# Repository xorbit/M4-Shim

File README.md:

# M4-Shim
ARM Cortex M4 shim for PoE-FeatherWing, functionally equivalent to Feather M4 Express

You can buy it now on [Tindie](https://www.tindie.com/products/silicognition/m4-shim/)
or on [Amazon](https://www.amazon.com/M4-Shim-Feather-PoE-FeatherWing-Ultra-Compact-Vertical/dp/B0971PKDV7/)!

### Description

This is an adaptation of the excellent
[Adafruit Feather M4 Express](https://github.com/adafruit/Adafruit-Feather-M4-Express-PCB),
redesigned specifically for use with the equally excellent
[PoE-FeatherWing](https://hackaday.io/project/168356-poe-featherwing).

The goal was to create a compact system with Power over Ethernet, Ethernet connectivity and
a powerful processor capable of supporting [CircuitPython](https://circuitpython.org/).
Because of the bulky RJ45 jack and flyback transformer on the PoE-FeatherWing, it was not
possible to mount a traditional Feather on top.  This redesign takes the relevant circuitry
of the Adafruit Feather M4 Express and shapes it so it fits in the gaps between the
tall components of the PoE-FeatherWing.  This way it can be mounted on top for an extremely
compact solution.

The only thing missing versus the Feather M4 Express is the battery support circuitry,
which did not seem necessary in a PoE design.

The hardware is sold with the [UF2 bootloader](https://github.com/adafruit/uf2-samdx1)
and [CircuitPython](https://github.com/adafruit/circuitpython) pre-installed.

### License

This redesign by Silicognition LLC is licensed as Creative Commons Attribution/Share-Alike,
just like the Adafruit Feather M4 Express it is based on.

Original Adafruit license statement:

Adafruit invests time and resources providing this open source design, please support Adafruit and open-source hardware by purchasing products from [Adafruit](https://www.adafruit.com)!

Designed by Limor Fried/Ladyada for Adafruit Industries.

Creative Commons Attribution/Share-Alike, all text above must be included in any redistribution. See LICENSE for additional details.

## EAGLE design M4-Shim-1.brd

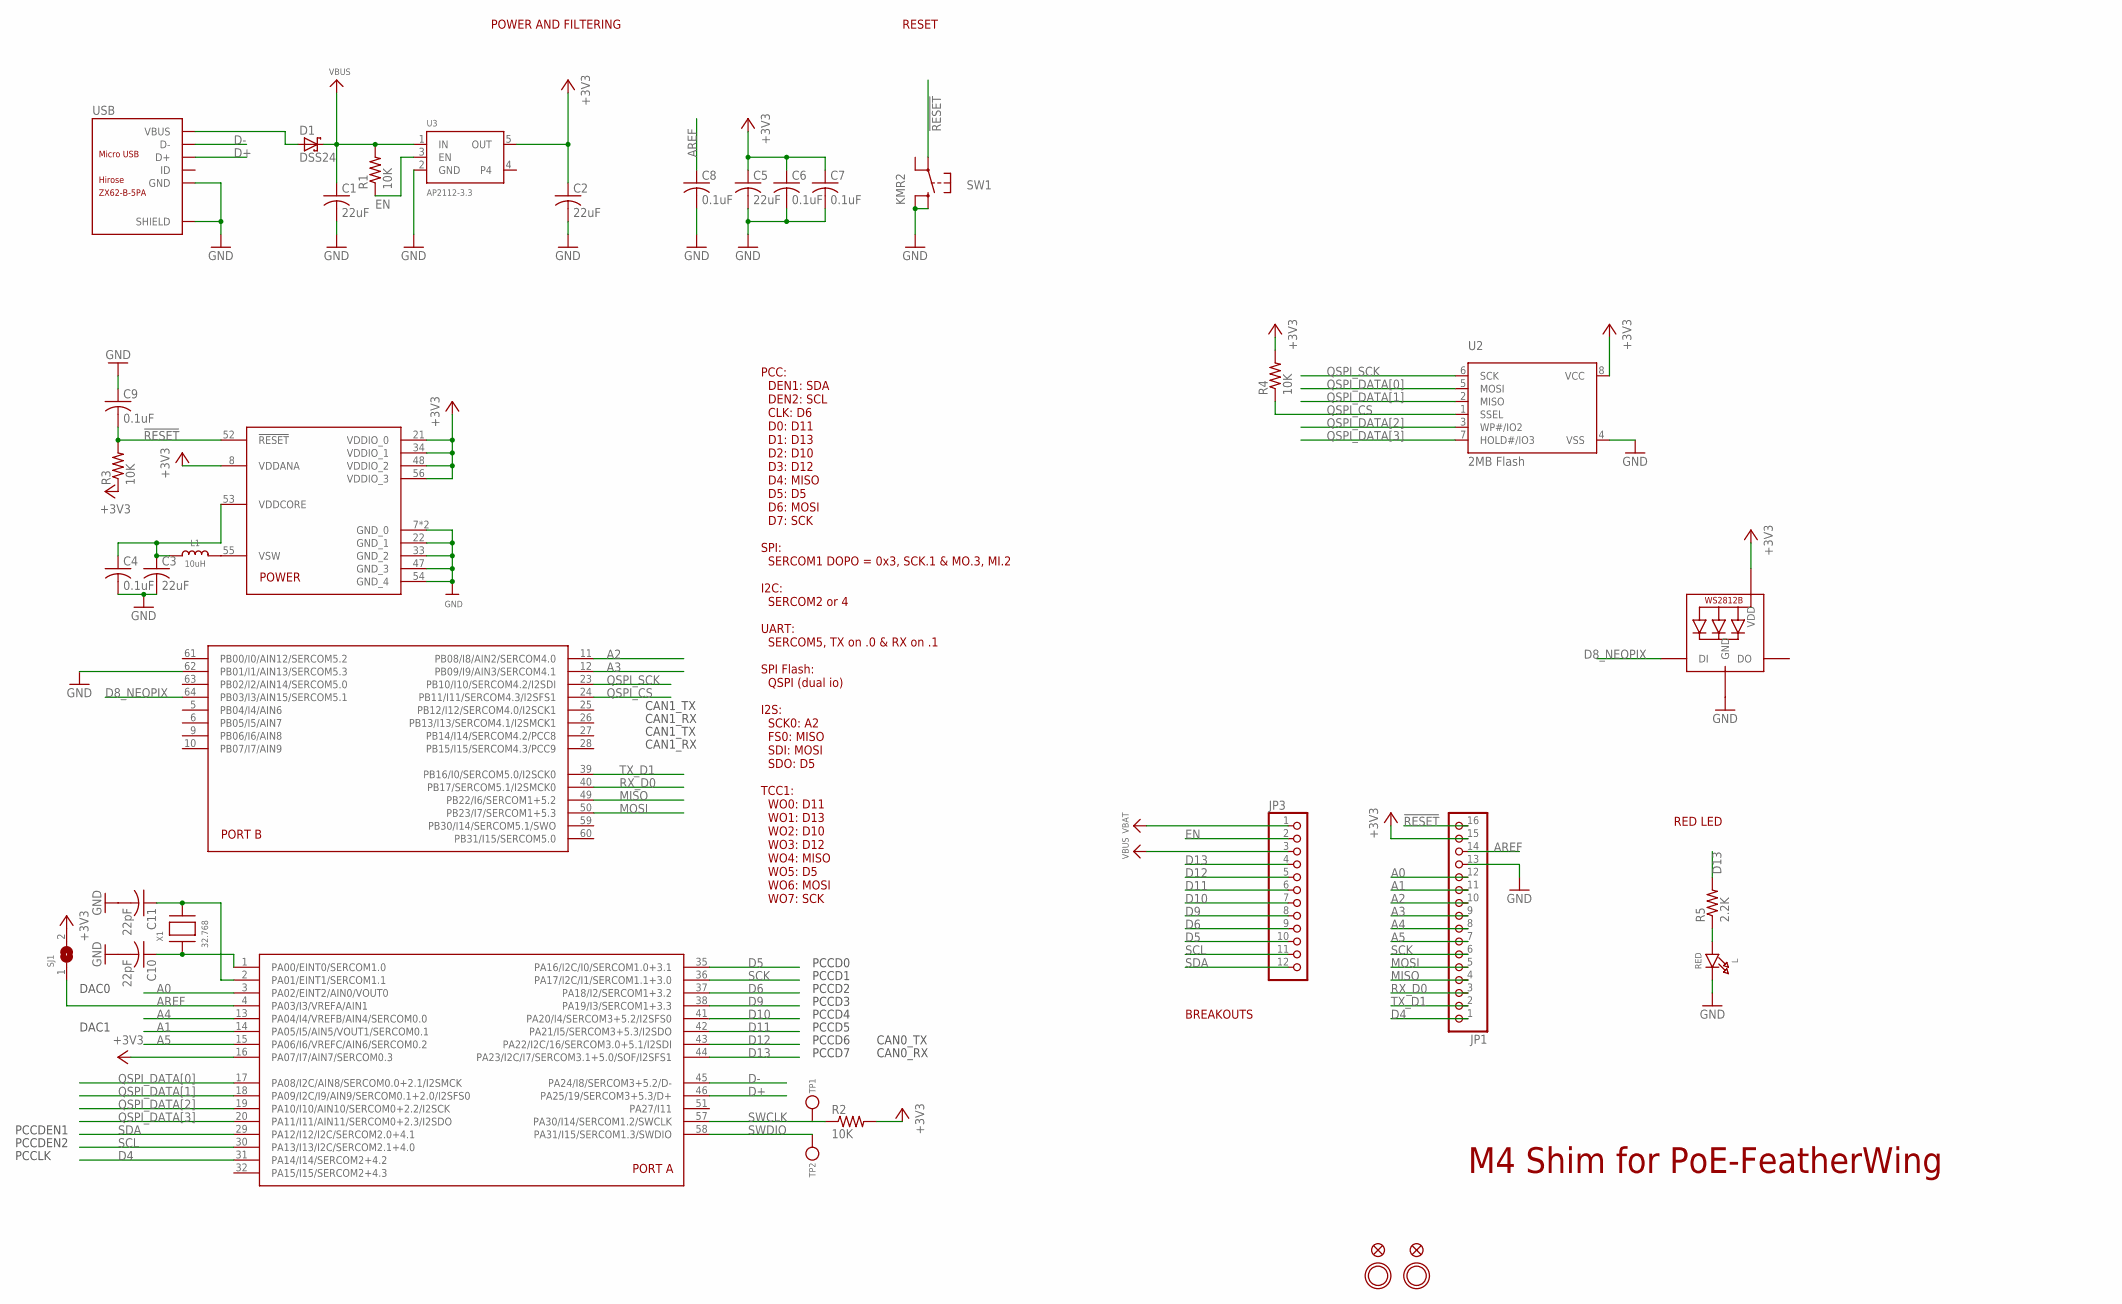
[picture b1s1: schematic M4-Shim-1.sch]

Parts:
C1, C2, C3, C5: 22uF; C0805K
C4, C6, C7, C8, C9: 0.1uF; C0402K
C10, C11: 22pF; C0402K
D1: DSS24; SOD123FL
JP1: HEADER-1X16ROUND; 1X16_ROUND
JP3: HEADER-1X12; 1X12_ROUND
L: RED; CHIPLED_0805_NOOUTLINE
L1: 10uH; INDUCTOR_1007
LED1: WS2812B3535; LED3535
R1, R2, R3, R4: 10K; R0402
R5: 2.2K; R0402
SJ1: SOLDERJUMPERCLOSED; SOLDERJUMPER_CLOSEDWIRE
SW1: KMR2; BTN_KMR2_4.6X2.8
TP1, TP2: TESTPOINTROUND1.5MM; TESTPOINT_ROUND_1.5MM
U1: ATSAMD51J; PQFN64-1
U2: 2MB Flash; USON8
U3: AP2112-3.3; SOT23-5
U$31, U$32: MOUNTINGHOLE2.5; MOUNTINGHOLE_2.5_PLATED
U$34, U$35: FIDUCIAL_1MM
USB: ZX62-B-5PA; MICRO-USB5+6P-SMD-0.65-AB
X1: 32.768; XTAL3215

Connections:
!RESET: C9.2, JP1.16, R3.2, SW1.A, U1.52 (!RESET)
+3V3: C2.1, C5.1, C6.1, C7.1, JP1.15, LED1.2 (VDD), R2.2, R3.1, R4.2, SJ1.2, U1.8 (VDDANA), U1.16 (PA07/I7/AIN7/SERCOM0.3), U1.21 (VDDIO_0), U1.34 (VDDIO_1), U1.48 (VDDIO_2), U1.56 (VDDIO_3), U2.8 (VCC), U3.5 (OUT)
A0: JP1.12, U1.3 (PA02/EINT2/AIN0/VOUT0)
A1: JP1.11, U1.14 (PA05/I5/AIN5/VOUT1/SERCOM0.1)
A2: JP1.10, U1.11 (PB08/I8/AIN2/SERCOM4.0)
A3: JP1.9, U1.12 (PB09/I9/AIN3/SERCOM4.1)
A4: JP1.8, U1.13 (PA04/I4/VREFB/AIN4/SERCOM0.0)
A5: JP1.7, U1.15 (PA06/I6/VREFC/AIN6/SERCOM0.2)
AREF: C8.1, JP1.14, SJ1.1, U1.4 (PA03/I3/VREFA/AIN1)
D4: JP1.1, U1.31 (PA14/I14/SERCOM2+4.2)
D5: JP3.10, U1.35 (PA16/I2C/I0/SERCOM1.0+3.1)
D6: JP3.9, U1.37 (PA18/I2/SERCOM1+3.2)
D8_NEOPIX: LED1.1 (DI), U1.64 (PB03/I3/AIN15/SERCOM5.1)
D9: JP3.8, U1.38 (PA19/I3/SERCOM1+3.3)
D10: JP3.7, U1.41 (PA20/I4/SERCOM3+5.2/I2SFS0)
D11: JP3.6, U1.42 (PA21/I5/SERCOM3+5.3/I2SDO)
D12: JP3.5, U1.43 (PA22/I2C/16/SERCOM3.0+5.1/I2SDI)
D13: JP3.4, R5.2, U1.44 (PA23/I2C/I7/SERCOM3.1+5.0/SOF/I2SFS1)
D+: U1.46 (PA25/19/SERCOM3+5.3/D+), USB.3 (D+)
D-: U1.45 (PA24/I8/SERCOM3+5.2/D-), USB.2 (D-)
EN: JP3.2, R1.1, U3.3 (EN)
GND: C1.2, C2.2, C3.2, C4.2, C5.2, C6.2, C7.2, C8.2, C9.1, C10.2, C11.2, JP1.13, L.C, LED1.4 (GND), SW1.B (S), SW1.B' (S1), U1.7 (GND_0), U1.22 (GND_1), U1.33 (GND_2), U1.47 (GND_3), U1.54 (GND_4), U1.62 (PB01/I1/AIN13/SERCOM5.3), U1.EXP (GND_0), U2.4 (VSS), U3.2 (GND), USB.5 (GND), USB.P1 (SHIELD), USB.P2 (SHIELD), USB.P3 (SHIELD), USB.P4 (SHIELD), USB.P5 (SHIELD), USB.P6 (SHIELD)
MISO: JP1.4, U1.49 (PB22/I6/SERCOM1+5.2)
MOSI: JP1.5, U1.50 (PB23/I7/SERCOM1+5.3)
unnamed: L.A, R5.1
unnamed: C10.1, U1.1 (PA00/EINT0/SERCOM1.0), X1.P$1
unnamed: C11.1, U1.2 (PA01/EINT1/SERCOM1.1), X1.P$2
unnamed: L1.P$2 (2), U1.55 (VSW)
QSPI_CS: R4.1, U1.24 (PB11/I11/SERCOM4.3/I2SFS1), U2.1 (SSEL)
QSPI_DATA[0]: U1.17 (PA08/I2C/AIN8/SERCOM0.0+2.1/I2SMCK), U2.5 (MOSI)
QSPI_DATA[1]: U1.18 (PA09/I2C/I9/AIN9/SERCOM0.1+2.0/I2SFS0), U2.2 (MISO)
QSPI_DATA[2]: U1.19 (PA10/I10/AIN10/SERCOM0+2.2/I2SCK), U2.3 (WP#/IO2)
QSPI_DATA[3]: U1.20 (PA11/I11/AIN11/SERCOM0+2.3/I2SDO), U2.7 (HOLD#/IO3)
QSPI_SCK: U1.23 (PB10/I10/SERCOM4.2/I2SDI), U2.6 (SCK)
RX_D0: JP1.3, U1.40 (PB17/SERCOM5.1/I2SMCK0)
SCK: JP1.6, U1.36 (PA17/I2C/I1/SERCOM1.1+3.0)
SCL: JP3.11, U1.30 (PA13/I13/I2C/SERCOM2.1+4.0)
SDA: JP3.12, U1.29 (PA12/I12/I2C/SERCOM2.0+4.1)
SWCLK: R2.1, TP1.P$1, U1.57 (PA30/I14/SERCOM1.2/SWCLK)
SWDIO: TP2.P$1, U1.58 (PA31/I15/SERCOM1.3/SWDIO)
TX_D1: JP1.2, U1.39 (PB16/I0/SERCOM5.0/I2SCK0)
VBAT: JP3.1
VBUS: C1.1, D1.C, JP3.3, R1.2, U3.1 (IN)
VBUSEXT: D1.A, USB.1 (VBUS)
VDDCORE1: C3.1, C4.1, L1.P$1 (1), U1.53 (VDDCORE)

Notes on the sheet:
POWER AND FILTERING
RESET
BREAKOUTS
RED LED
PCCDEN1
PCCDEN2
PCCD0
PCCD1
PCCD2
PCCD3
PCCD4
PCCD5
PCCD6
PCCD7
PCCLK
PCC: DEN1: SDA DEN2: SCL CLK: D6 D0: D11 D1: D13 D2: D10 D3: D12 D4: MISO D5: D5 D6: MOSI D7: SCK SPI: SERCOM1 DOPO = 0x3, SCK.1 & MO.3, MI.2 I2C: SERCOM2 or 4 UART: SERCOM5, TX on .0 & RX on .1 SPI Flash: QSPI (dual io) I2S: SCK0: A2 FS0: MISO SDI: MOSI SDO: D5 TCC1: WO0: D11 WO1: D13 WO2: D10 WO3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
CAN0_TX
CAN0_RX
DAC0
DAC1
CAN1_TX
CAN1_RX
M4 Shim for PoE-FeatherWing

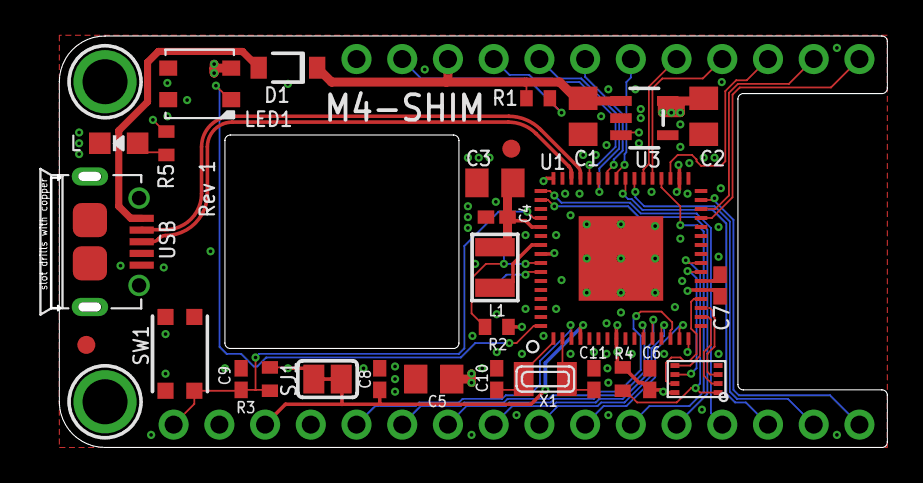
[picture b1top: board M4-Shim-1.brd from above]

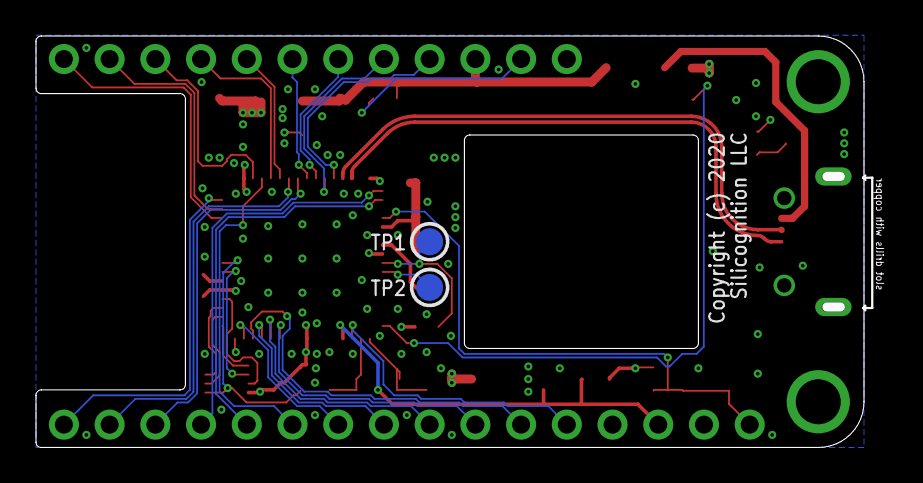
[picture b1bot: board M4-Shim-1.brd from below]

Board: 4 copper layers, 46.8 x 22.4 mm, 35 parts (2 on the bottom side), 44 nets.

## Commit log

2021-01-28 Initial commit of rev 1 and rev 2
2021-01-30 Add software links for UF2 bootloader and CircuitPython
2021-07-14 Update README with buy links
2021-12-28 Add PDF of rev 2 schematic

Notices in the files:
M4-Shim-1.brd:
Copyright (c) 2020
parts and their libraries:
microbuilder: This work is placed in the public domain, and may be freely used for commercial and non-commercial work with the following conditions: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
